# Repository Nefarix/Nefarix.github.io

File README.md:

Internet of Things Project
==========================

This is a demonstration of a MarkDown (.md) README file.

In order to create a .pdf from .md use:
https://github.com/jgm/pandoc/releases/download/1.16.0.2/pandoc-1.16.0.2-windows.msi

http://www.texts.io/Texts-1.3.2.msi

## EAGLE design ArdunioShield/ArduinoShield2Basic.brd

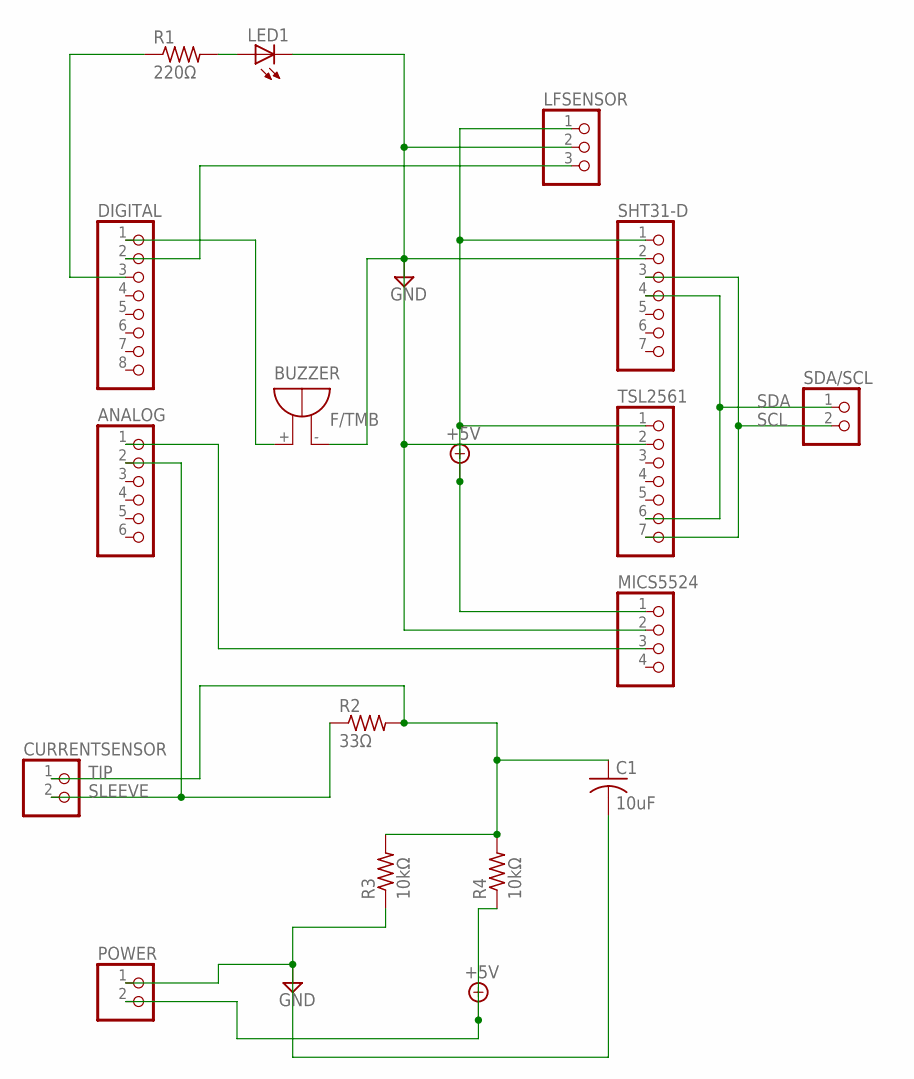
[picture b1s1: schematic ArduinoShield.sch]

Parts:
ANALOG: PINHD-1X6; 1X06
BUZZER: F/TMB
C1: 10uF; C025-060X050
CURRENTSENSOR: PINHD-1X2; 1X02
DIGITAL: PINHD-1X8; 1X08
LED1: LED5MM
LFSENSOR: PINHD-1X3; 1X03
MICS5524: PINHD-1X4; 1X04
POWER: PINHD-1X2; 1X02
R1: 220Ω; 0309/12
R2: 33Ω; 0309/12
R3, R4: 10kΩ; 0309/12
SDA/SCL: PINHD-1X2; 1X02
SHT31-D: PINHD-1X7; 1X07
TSL2561: PINHD-1X7; 1X07

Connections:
+5V: LFSENSOR.1, MICS5524.1, POWER.2, R4.1, SHT31-D.1, TSL2561.1
GND: BUZZER.-, C1.2, LED1.K (C), LFSENSOR.2, MICS5524.2, POWER.1, R3.1, SHT31-D.2, TSL2561.2
unnamed: ANALOG.1, MICS5524.3
unnamed: LED1.A, R1.2
unnamed: BUZZER.+, DIGITAL.1
unnamed: DIGITAL.2, LFSENSOR.3
unnamed: DIGITAL.3, R1.1
SCL: SDA/SCL.2, SHT31-D.3, TSL2561.7
SDA: SDA/SCL.1, SHT31-D.4, TSL2561.6
SLEEVE: ANALOG.2, CURRENTSENSOR.2, R2.1
TIP: C1.1, CURRENTSENSOR.1, R2.2, R3.2, R4.2

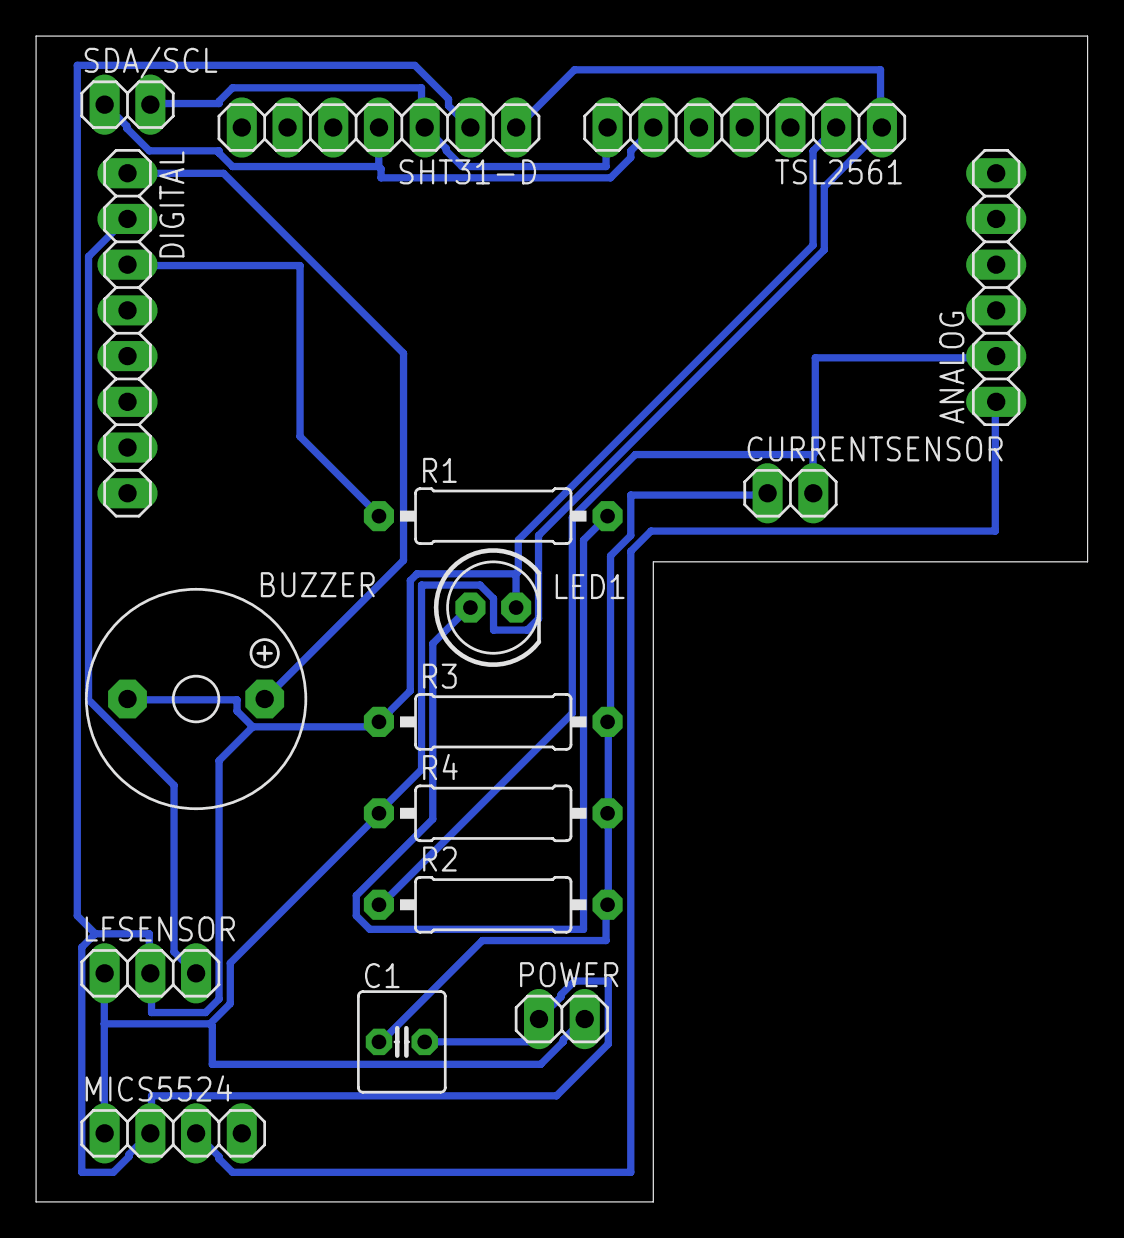
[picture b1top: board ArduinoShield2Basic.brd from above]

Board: 2 copper layers, 58.4 x 64.8 mm, 16 parts (0 on the bottom side), 11 nets.

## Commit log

2016-09-06 :space_invader: Added .gitattributes
2016-09-06 Index Files taken from six0four, base formats for site
2016-09-06 Images of Blinking LEDS
    First Experiment with Raspberry PI
2016-09-20 Trying to fix site
    Does it work?!
2016-09-27 Please?
    Fixing site
2016-09-27 fix sit pls
2016-10-04 Making Blog Section
    Making Blog Section
2016-10-04 getting image on blog
    led blinking
2016-10-04 Size restricting the image
    image
2016-10-11 Adding Images to blog
    Purchase, and previous work
2016-10-11 Fixed Image
    Wrong image before
2016-10-11 Project Update - Week6
    Schedule is being followed. Finances are good, no problems as of yet,
    parts are being ordered
2016-10-25 Placard Link
    Linked from vishwas' github
2016-11-08 Progress Report # 2
    Posted PR#2
2016-11-08 Progress Report #2 Edited
    PR#2 Change
2016-11-15 Progress Report #3
2016-11-22 Week 12 Added (Menu Fixed as well)
    Blog week 12 and menu fix
2016-11-22 added my own repository link
    repository link
2016-11-29 Uploaded Files for presentation to GitHub
2016-11-29 Moved files to documentation
2016-11-29 minor fix
    hi
2016-11-29 trying to upload build video
2016-12-13 script
    script
2017-01-20 Addons
2018-04-25 addng pcb files
